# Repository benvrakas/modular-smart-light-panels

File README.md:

# Modular Smart Light Panels

Edge-lit hexagon, square and triangle light panels that snap together in any layout, work out their own arrangement, and play effects placed in the room rather than along a strip.

**Read the design in [SPEC.md](SPEC.md)**, with the reasons for each decision in [docs/decisions/](docs/decisions/). They are the only written description of the design; this page and the pictures only point into them. Progress toward the first prototype is tracked in [docs/roadmap-to-prototype.md](docs/roadmap-to-prototype.md).

| Close-up at an outside corner | Maximum brightness at night |
|---|---|
|  |  |

Other effects:

| Aurora | Sunset | Ocean |
|---|---|---|
|  |  |  |
| **Confetti** | **Warm white** | **Fire** |
|  |  |  |

Vertical (9:16):

| Outside corner | Painting wall | Inside corner |
|---|---|---|
|  |  |  |

Videos (1440p): [wide shot](docs/figures/video_wide.mp4) · [close-up](docs/figures/video_closeup.mp4).

## Where things are described

| Topic | Spec section | Pictures |
|---|---|---|
| Panels, shapes, optics | [§2](SPEC.md#2-physical-architecture--optical-design) |  |
| Seam contacts and bridge | [§3.3](SPEC.md#33-edge-contacts-and-bridge) |  |
| Edge and controller boards | [§3.5](SPEC.md#35-board-types-v60-decision-0009) |  |
| Topology discovery | [§4](SPEC.md#4-topology--orientation-discovery) | |
| Network, rendering, software | [§5–7](SPEC.md#5-network-topology) | |
| Power, brightness | [§8](SPEC.md#8-power-distribution--protection) |  |
| Mechanics (printed parts) | [§9](SPEC.md#9-mechanical) |  |

## Repository layout

```
SPEC.md                    The specification (version and changelog inside)
docs/
  decisions/               Decision records: context, options, choice, consequences
  figures/                 Generated pictures (make_figures.py); never edited by hand
  roadmap-to-prototype.md  Work packages and status
  gap-analysis.md, reviews/, mechanical/, datasheets/, bringup/, handoff/
  archive/explainer/       Retired HTML explainer (superseded by SPEC.md + figures)
hardware/                  KiCad 9: edge-board/, controller-board/, bridge/ (+ coupon/), lib/, archive/
mechanical/solidcraft/     Printed parts, assembly, STL/STEP exports, render/ (Blender scene scripts)
firmware/, software/       To be written
production/                Released fab packages, once ordered
```

Each design folder has its own notes (for example `hardware/edge-board/LAYOUT-NOTES.md`, `mechanical/solidcraft/README.md`) for how its files are built.

## Regenerating

- Figures: `python docs/figures/make_figures.py --all` (KiCad 3D views and SolidCraft snapshots, then the web copies).
- Renders: `python mechanical/solidcraft/render/render_batch.py` (Blender, GPU; slow). The penthouse scene file is not in git (over GitHub's file-size limit): get "Modern Loft Apartment" by Matteo Pascale from BlenderKit (free) into `mechanical/solidcraft/render/assets/penthouse/`, as described in `render/CREDITS.md`.

## License

Non-commercial use only: hardware, CAD and docs under CC BY-NC-SA 4.0, software under PolyForm Noncommercial 1.0.0. Details and third-party exceptions: [LICENSE.md](LICENSE.md).

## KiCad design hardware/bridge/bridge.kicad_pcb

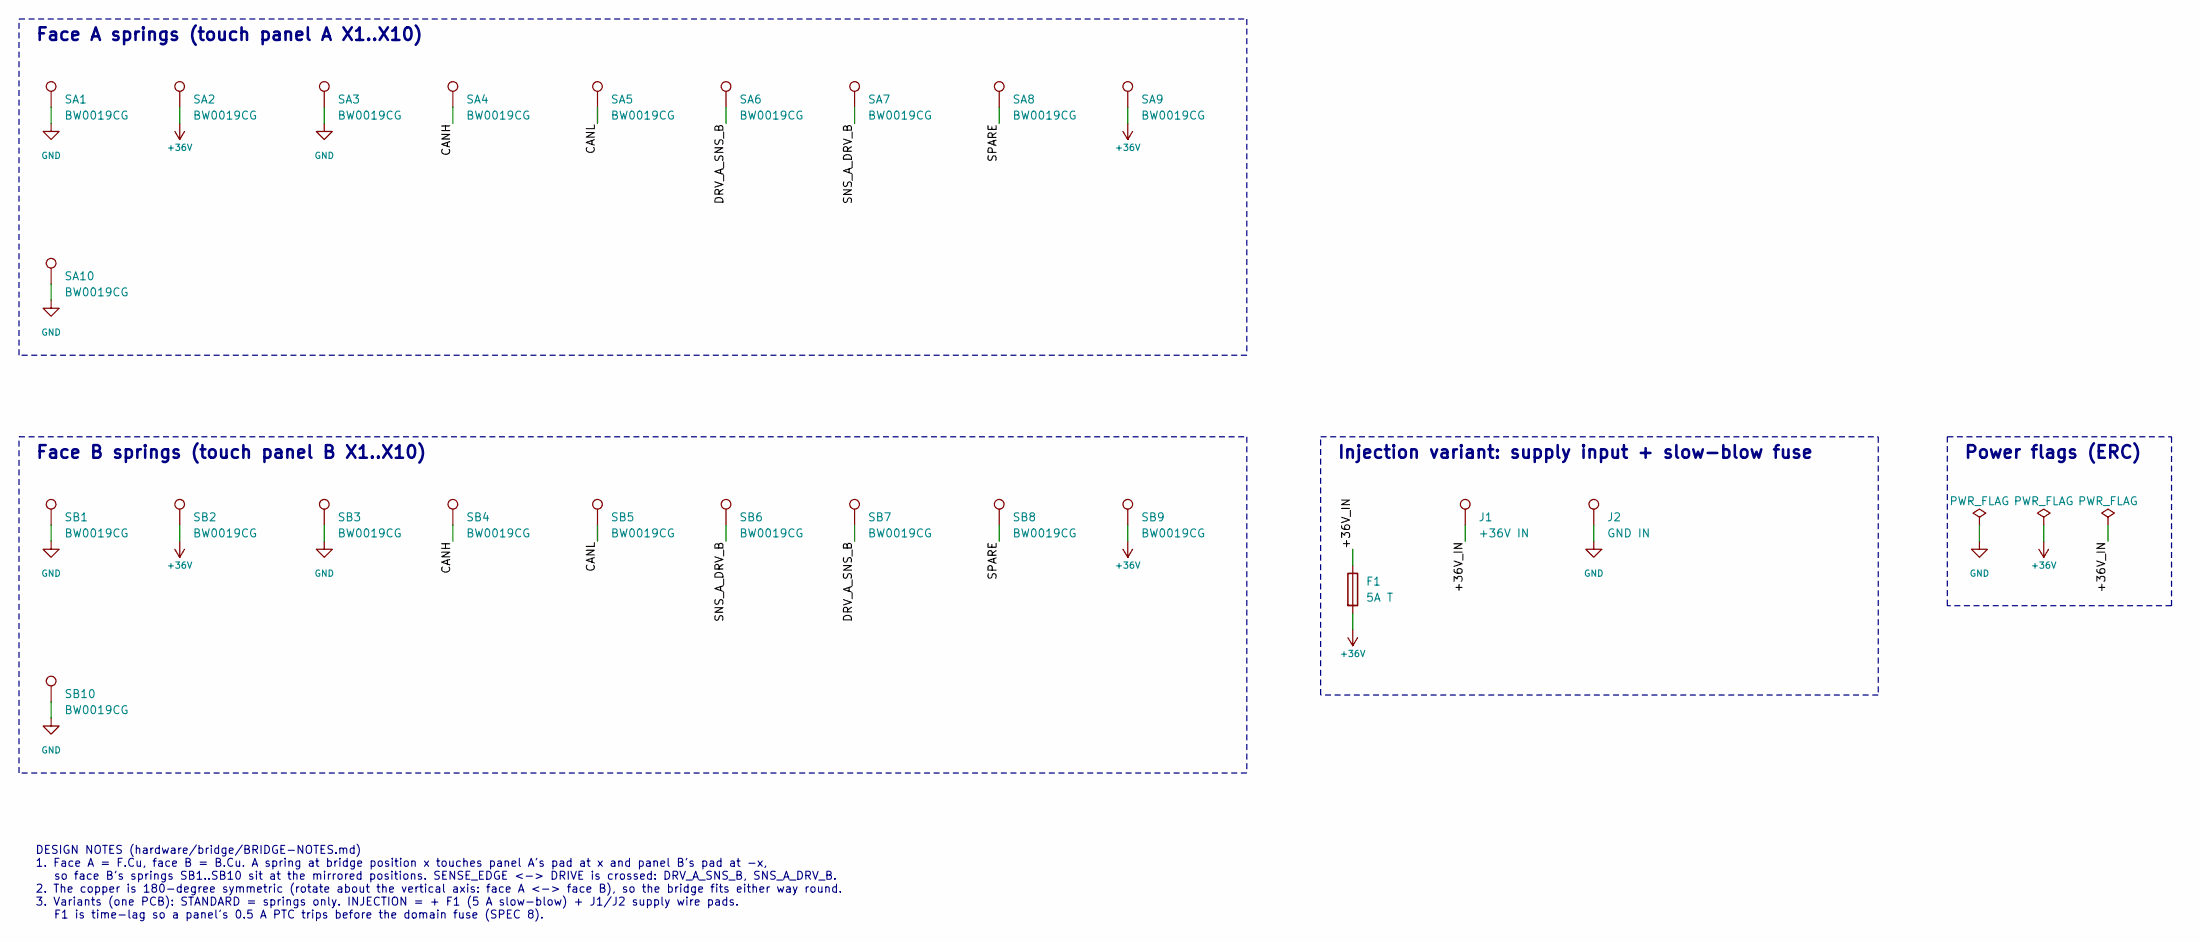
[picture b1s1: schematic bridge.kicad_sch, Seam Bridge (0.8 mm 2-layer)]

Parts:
F1: 5A T; Fuse_1206_3216Metric; MPN 0685T5000-01; LCSC C3163312
J1: +36V IN; SolderWire-0.75sqmm_1x01_D1.25mm_OD2.3mm
J2: GND IN; SolderWire-0.75sqmm_1x01_D1.25mm_OD2.3mm
SA1, SA2, SA3, SA4, SA5, SA6, SA7, SA8, SA9, SA10: BW0019CG; Spring_BW0019CG; MPN BW0019CG-L3.5W1.5H4.3; LCSC C2826517
SB1, SB2, SB3, SB4, SB5, SB6, SB7, SB8, SB9, SB10: BW0019CG; Spring_BW0019CG; MPN BW0019CG-L3.5W1.5H4.3; LCSC C2826517

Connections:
+36V: F1.2, SA2.1, SA9.1, SB2.1, SB9.1
/+36V_IN: F1.1, J1.1
/CANH: SA4.1, SB4.1
/CANL: SA5.1, SB5.1
/DRV_A_SNS_B: SA6.1, SB7.1
/SNS_A_DRV_B: SA7.1, SB6.1
/SPARE: SA8.1, SB8.1
GND: J2.1, SA1.1, SA3.1, SA10.1, SB1.1, SB3.1, SB10.1

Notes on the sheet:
Face A springs (touch panel A X1..X10)
Face B springs (touch panel B X1..X10)
Injection variant: supply input + slow-blow fuse
Power flags (ERC)
DESIGN NOTES (hardware/bridge/BRIDGE-NOTES.md) 1. Face A = F.Cu, face B = B.Cu. A spring at bridge position x touches panel A's pad at x and panel B's pad at -x, so face B's springs SB1..SB10 sit at the mirrored positions. SENSE_EDGE <-> DRIVE is crossed: DRV_A_SNS_B, SNS_A_DRV_B. 2. The copper is 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

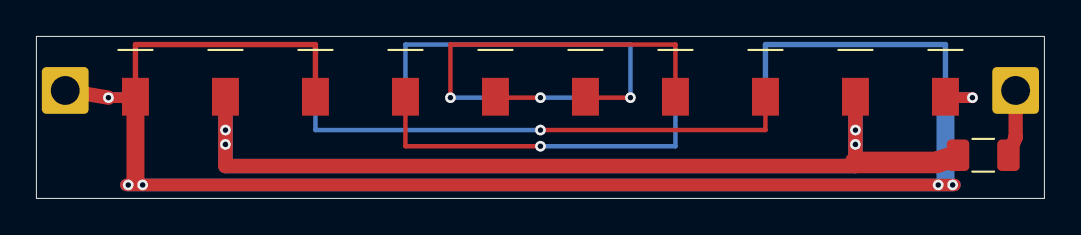
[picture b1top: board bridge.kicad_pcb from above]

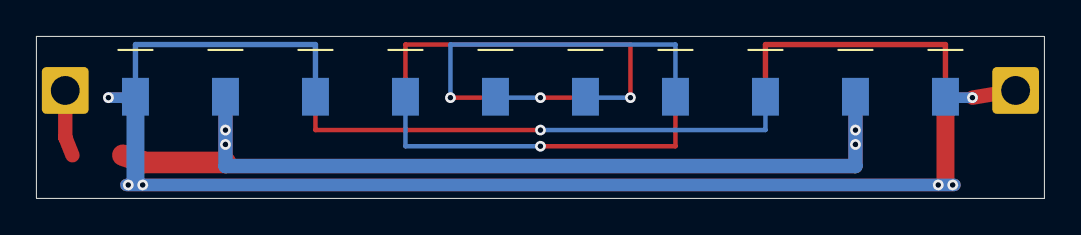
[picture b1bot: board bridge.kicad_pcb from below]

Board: 2 copper layers, 56.0 x 9.0 mm, 23 parts (10 on the bottom side), 8 nets.

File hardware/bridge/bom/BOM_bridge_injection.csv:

Comment,Designator,Footprint,LCSC
BW0019CG-L3.5W1.5H4.3,"SA1,SA2,SA3,SA4,SA5,SA6,SA7,SA8,SA9,SA10,SB1,SB2,SB3,SB4,SB5,SB6,SB7,SB8,SB9,SB10",Spring_BW0019CG,C2826517
0685T5000-01 5A slow-blow,F1,Fuse_1206_3216Metric,C3163312

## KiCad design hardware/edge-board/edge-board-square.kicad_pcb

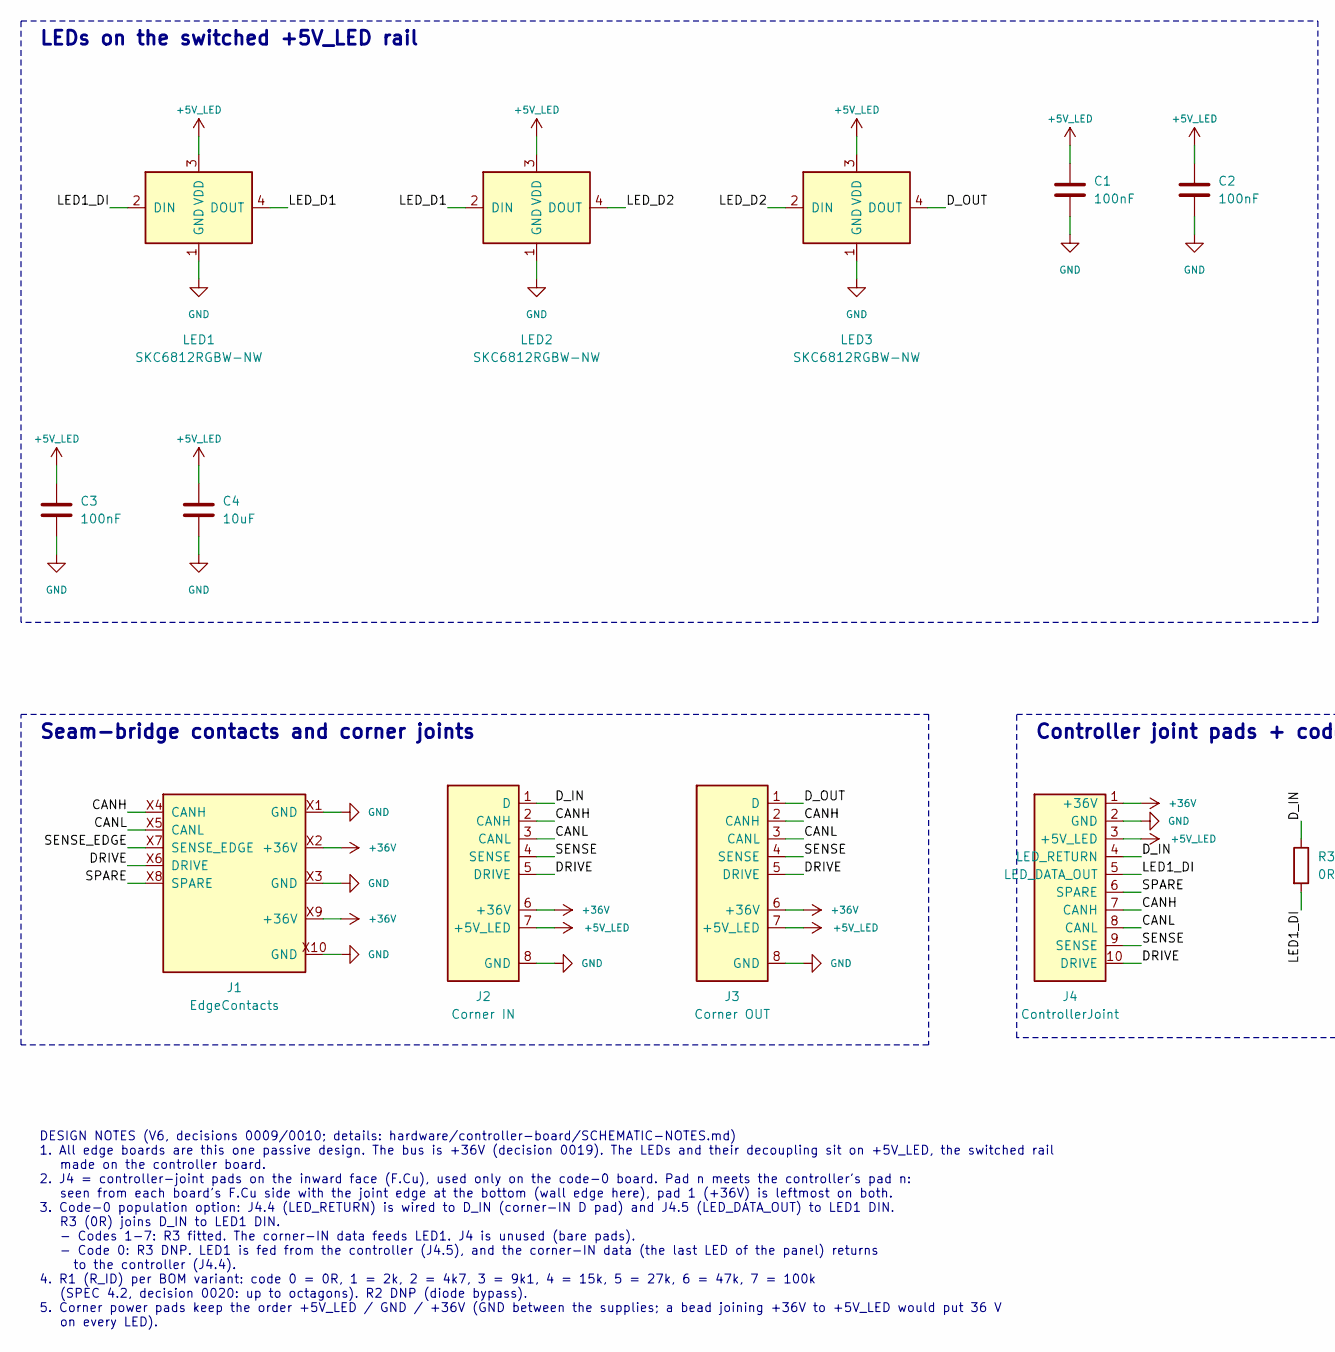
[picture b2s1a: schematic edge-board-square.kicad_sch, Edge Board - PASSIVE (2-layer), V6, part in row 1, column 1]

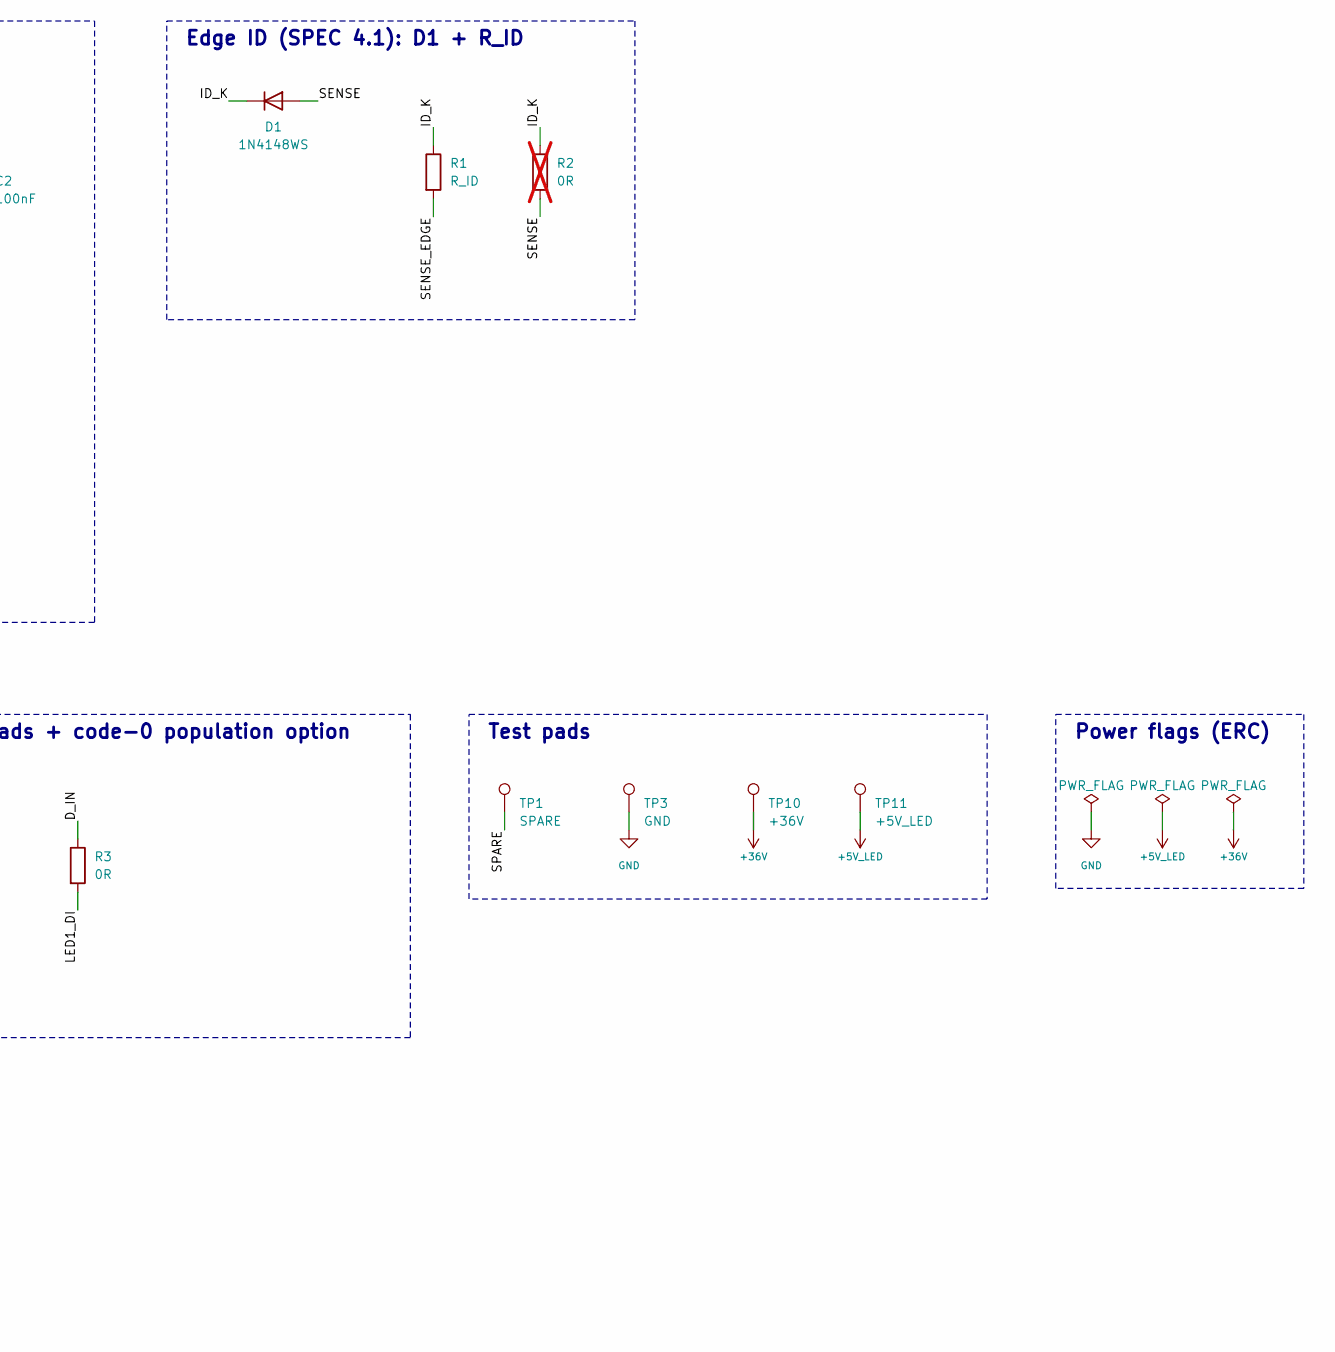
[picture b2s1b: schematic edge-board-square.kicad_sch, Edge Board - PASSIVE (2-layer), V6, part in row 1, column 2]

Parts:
C1, C2, C3: 100nF; C_0603_1608Metric; MPN CC0603KRX7R9BB104; LCSC C14663
C4: 10uF; C_0805_2012Metric; MPN CL21A106KAYNNNE; LCSC C15850
D1: 1N4148WS; D_SOD-323; MPN 1N4148WS; LCSC C2128
J1: EdgeContacts; EdgeContacts_SpringPads
J2: Corner IN; CornerJoint_L
J3: Corner OUT; CornerJoint_R
J4: ControllerJoint; ControllerJoint_EdgeBoard
LED1, LED2, LED3: SKC6812RGBW-NW; LED_SKC6812RGBW_5050-4; MPN SKC6812RGBW-NW; LCSC C5348912
R1: R_ID; R_0603_1608Metric; MPN 0603WAF2001T5E; LCSC C22975
R2: 0R; R_0603_1608Metric; MPN 0603WAF0000T5E; LCSC C21189; not fitted
R3: 0R; R_0402_1005Metric; MPN 0402WGF0000TCE; LCSC C17168
TP1: SPARE; TestPoint_Pad_D1.5mm
TP3: GND; TestPoint_Pad_D1.5mm
TP10: +36V; TestPoint_Pad_D1.5mm
TP11: +5V_LED; TestPoint_Pad_D1.5mm

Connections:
+5V_LED: C1.1, C2.1, C3.1, C4.1, J2.7 (+5V_LED), J3.7 (+5V_LED), J4.3 (+5V_LED), LED1.3 (VDD), LED2.3 (VDD), LED3.3 (VDD), TP11.1
+36V: J1.X2 (+36V), J1.X9 (+36V), J2.6 (+36V), J3.6 (+36V), J4.1 (+36V), TP10.1
/CANH: J1.X4 (CANH), J2.2 (CANH), J3.2 (CANH), J4.7 (CANH)
/CANL: J1.X5 (CANL), J2.3 (CANL), J3.3 (CANL), J4.8 (CANL)
/DRIVE: J1.X6 (DRIVE), J2.5 (DRIVE), J3.5 (DRIVE), J4.10 (DRIVE)
/D_IN: J2.1 (D), J4.4 (LED_RETURN), R3.1
/D_OUT: J3.1 (D), LED3.4 (DOUT)
/ID_K: D1.1 (K), R1.1, R2.1
/LED1_DI: J4.5 (LED_DATA_OUT), LED1.2 (DIN), R3.2
/LED_D1: LED1.4 (DOUT), LED2.2 (DIN)
/LED_D2: LED2.4 (DOUT), LED3.2 (DIN)
/SENSE: D1.2 (A), J2.4 (SENSE), J3.4 (SENSE), J4.9 (SENSE), R2.2
/SENSE_EDGE: J1.X7 (SENSE_EDGE), R1.2
/SPARE: J1.X8 (SPARE), J4.6 (SPARE), TP1.1
GND: C1.2, C2.2, C3.2, C4.2, J1.X1 (GND), J1.X3 (GND), J1.X10 (GND), J2.8 (GND), J3.8 (GND), J4.2 (GND), LED1.1 (GND), LED2.1 (GND), LED3.1 (GND), TP3.1

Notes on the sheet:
LEDs on the switched +5V_LED rail
Edge ID (SPEC 4.1): D1 + R_ID
Seam-bridge contacts and corner joints
Controller joint pads + code-0 population option
Test pads
Power flags (ERC)
DESIGN NOTES (V6, decisions 0009/0010; details: hardware/controller-board/SCHEMATIC-NOTES.md) 1. All edge boards are this one passive design. The bus is +36V (decision 0019). The LEDs and their decoupling sit on +5V_LED, the switched rail made on the controller board. 2. J4 = controller-joint pads 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

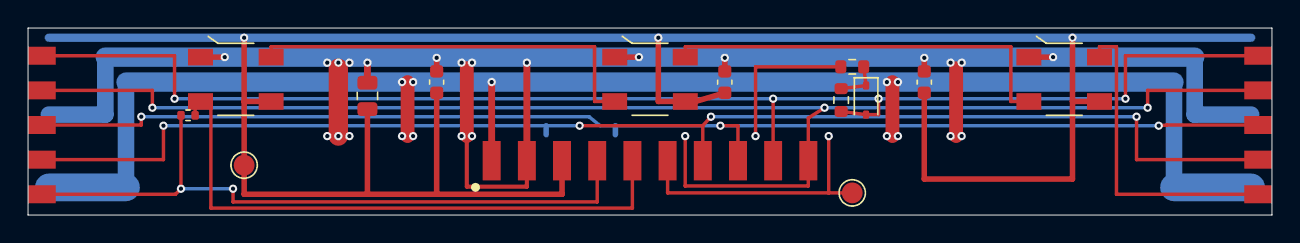
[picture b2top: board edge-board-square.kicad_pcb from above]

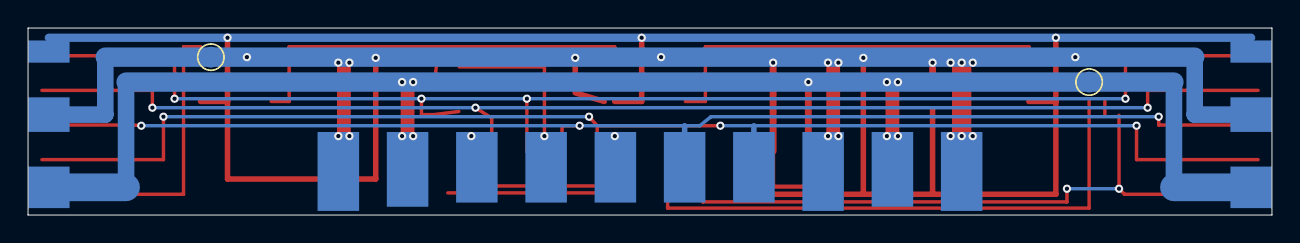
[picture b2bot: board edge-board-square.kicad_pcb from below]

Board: 2 copper layers, 89.8 x 13.5 mm, 19 parts (2 on the bottom side), 15 nets.

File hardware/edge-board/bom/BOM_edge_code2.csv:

Comment,Designator,Footprint,LCSC
100nF,"C1,C2,C3",C_0603_1608Metric,C14663
10uF,C4,C_0805_2012Metric,C15850
1N4148WS,D1,D_SOD-323,C2128
SKC6812RGBW-NW,"LED1,LED2,LED3",LED_SKC6812RGBW_5050-4,C5348912
2k7,R1,R_0603_1608Metric,C13167
0R,R3,R_0402_1005Metric,C17168

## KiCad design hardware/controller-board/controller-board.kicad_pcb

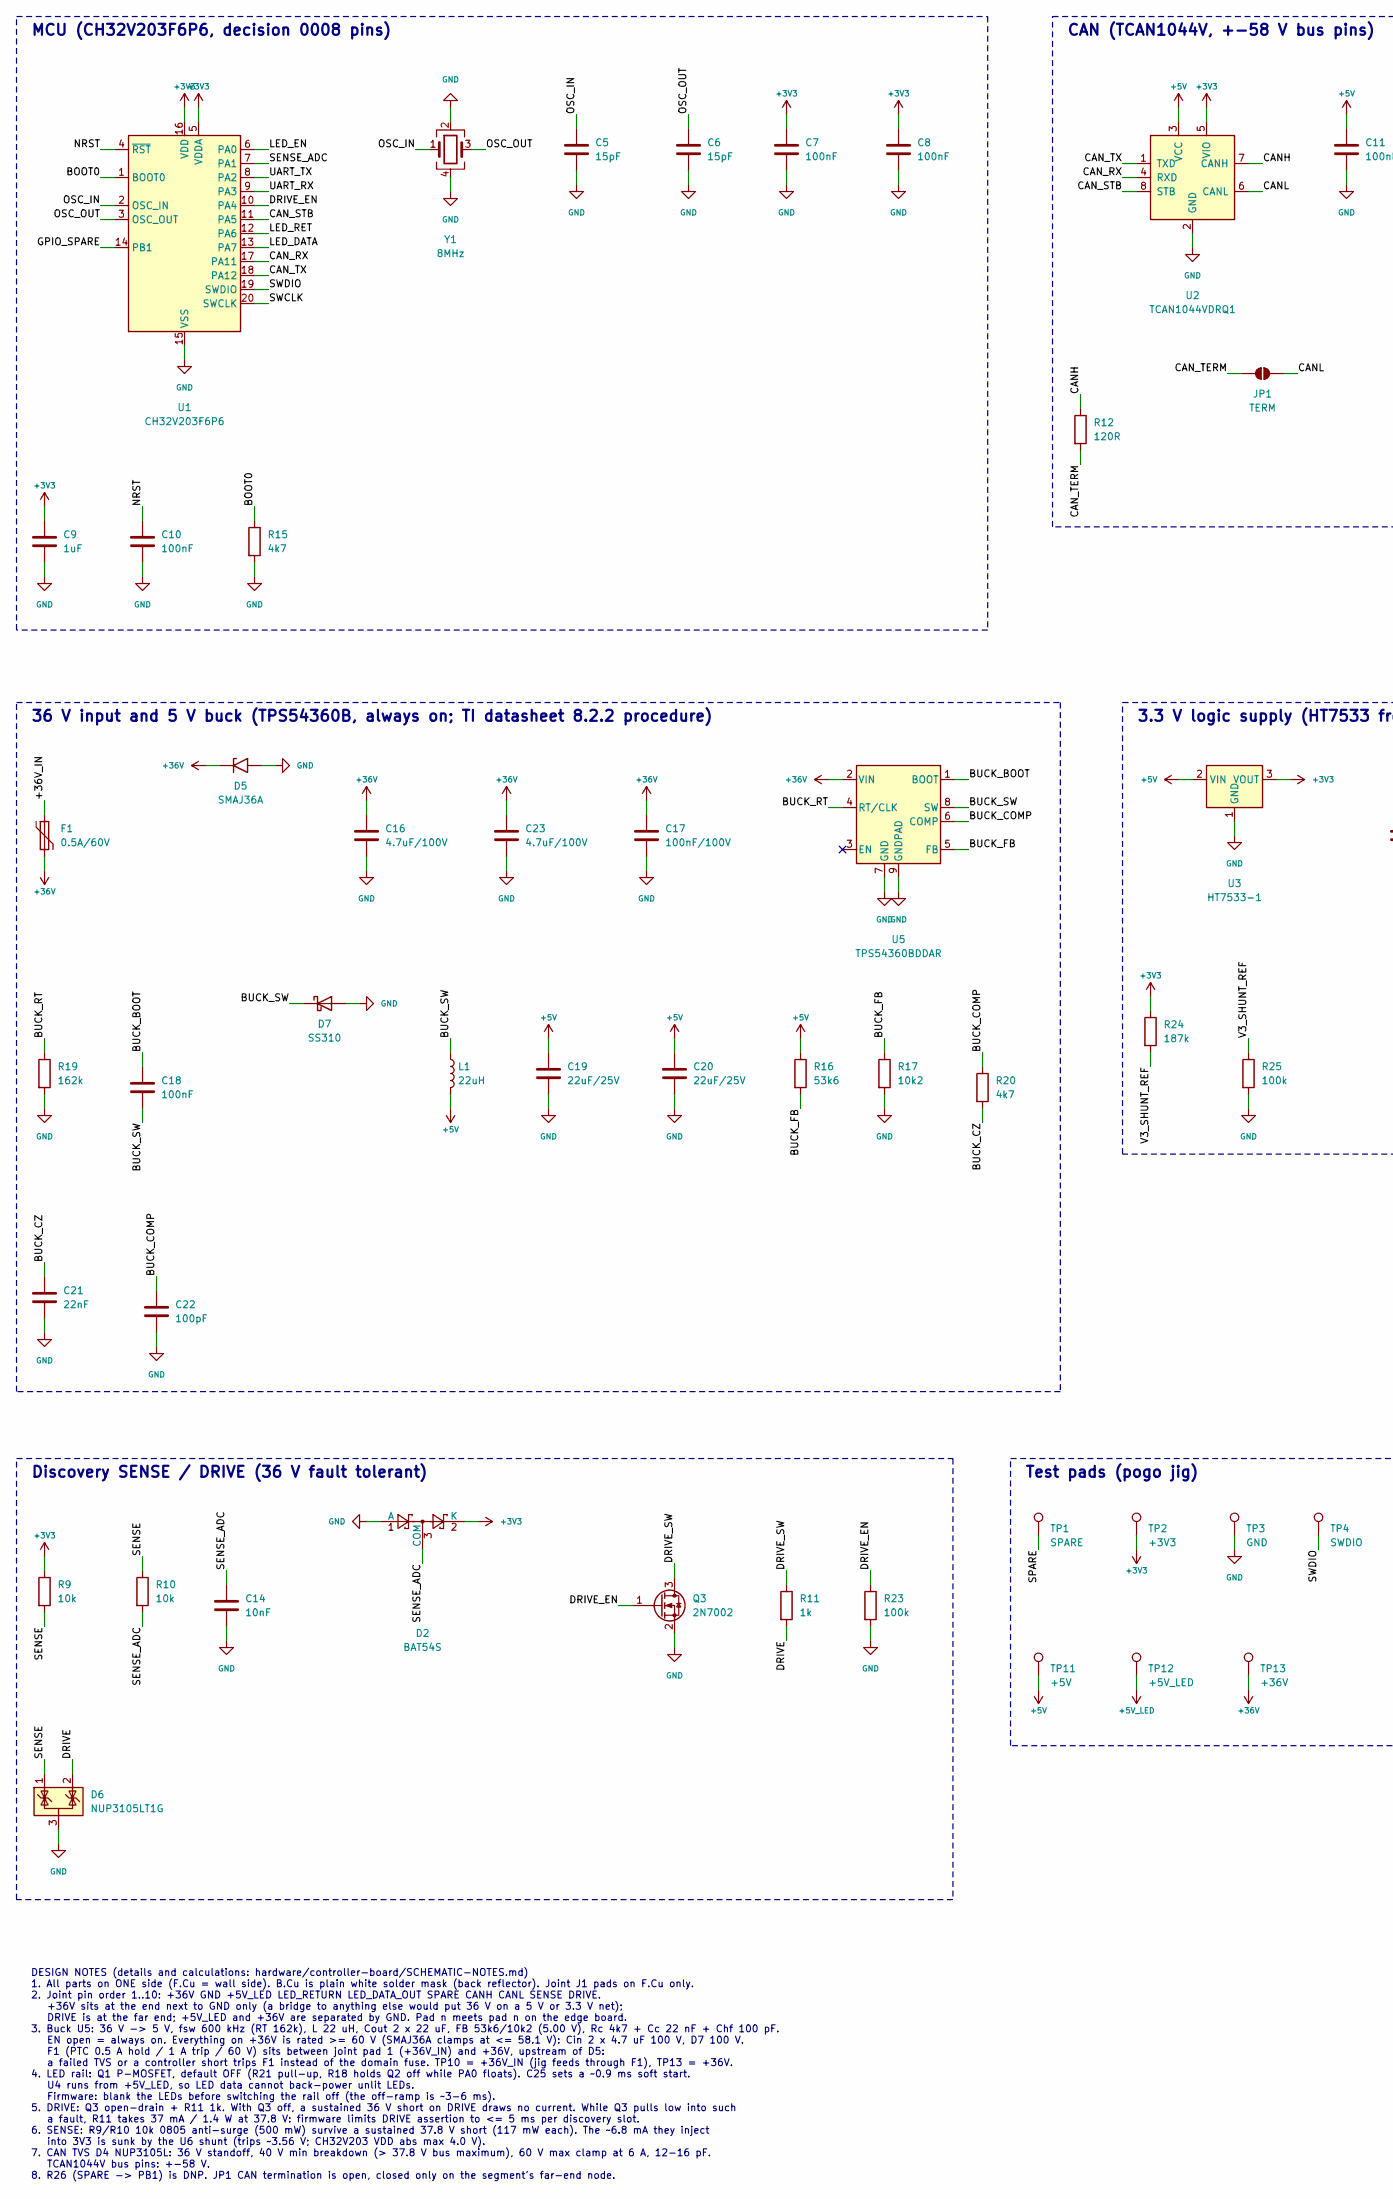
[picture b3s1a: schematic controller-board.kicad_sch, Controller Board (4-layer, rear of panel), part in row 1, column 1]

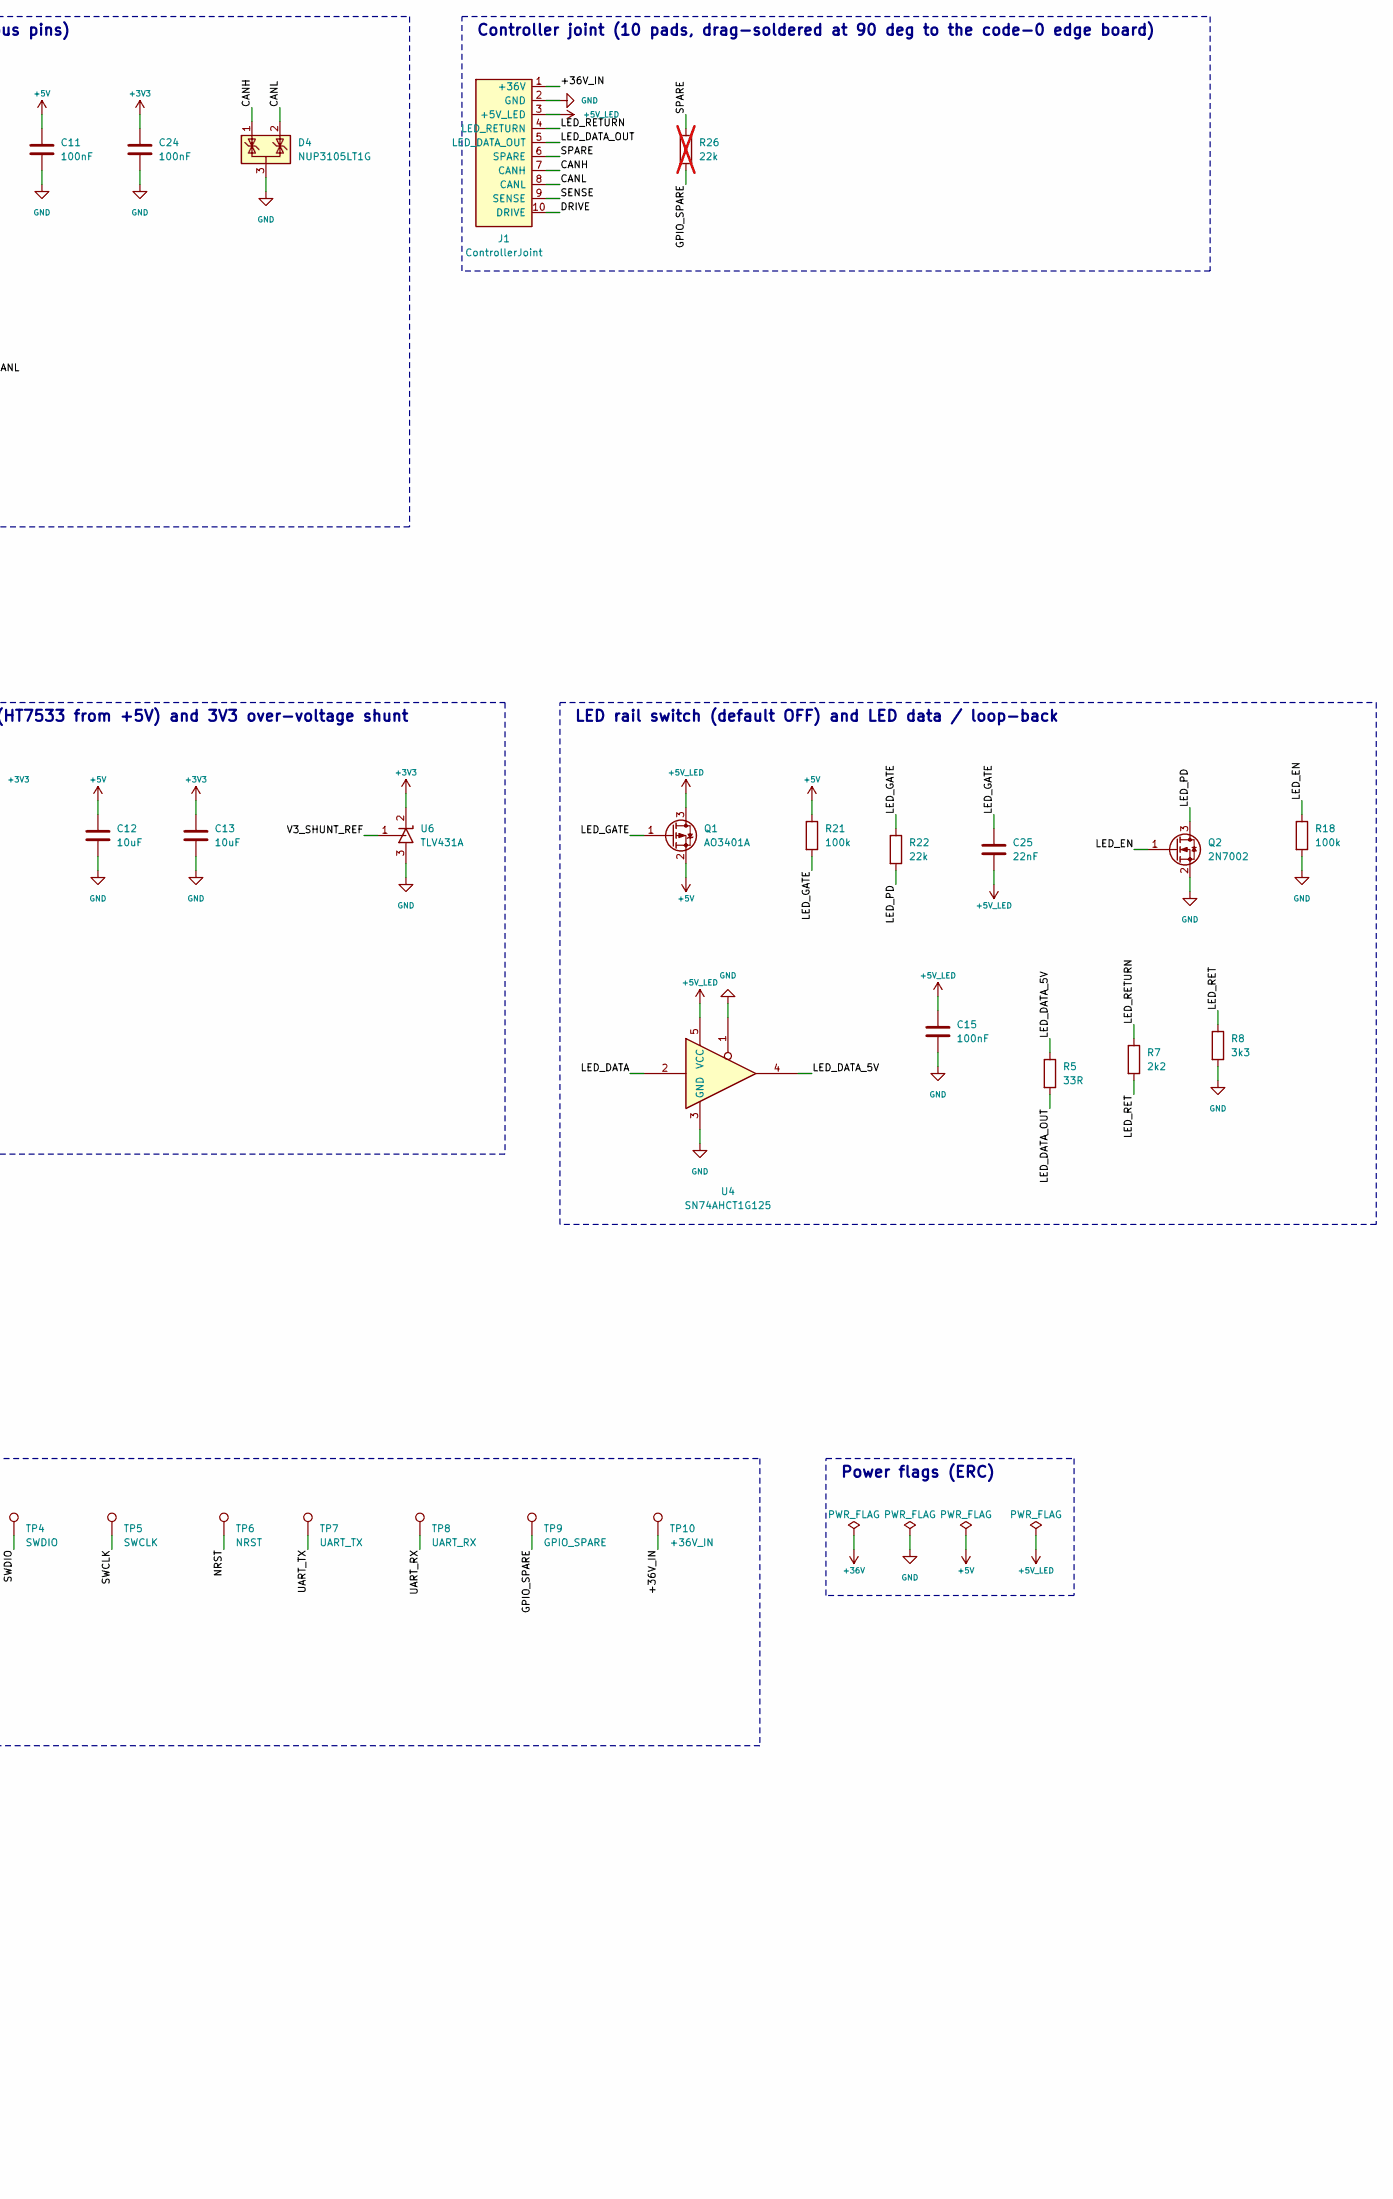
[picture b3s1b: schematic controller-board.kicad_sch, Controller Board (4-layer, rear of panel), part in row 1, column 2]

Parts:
C5, C6: 15pF; C_0603_1608Metric; MPN CL10C150JB8NNNC; LCSC C1644
C7, C8, C10, C11, C15, C18, C24: 100nF; C_0603_1608Metric; MPN CC0603KRX7R9BB104; LCSC C14663
C9: 1uF; C_0603_1608Metric; MPN CL10A105KB8NNNC; LCSC C15849
C12, C13: 10uF; C_0805_2012Metric; MPN CL21A106KAYNNNE; LCSC C15850
C14: 10nF; C_0603_1608Metric; MPN 0603B103K500NT; LCSC C57112
C16, C23: 4.7uF/100V; C_1206_3216Metric; MPN GRM31CC72A475KE11L; LCSC C237304
C17: 100nF/100V; C_0603_1608Metric; MPN CL10B104KC8NNNC; LCSC C15725
C19, C20: 22uF/25V; C_0805_2012Metric; MPN CL21A226MAQNNNE; LCSC C45783
C21, C25: 22nF; C_0603_1608Metric; MPN CL10B223KB8NNNC; LCSC C21122
C22: 100pF; C_0603_1608Metric; MPN CL10C101JB8NNNC; LCSC C14858
D2: BAT54S; SOT-23; MPN BAT54S,215; LCSC C47546
D4, D6: NUP3105LT1G; SOT-23; MPN NUP3105LT1G; LCSC C22390031
D5: SMAJ36A; D_SMA; MPN SMAJ36A-13-F; LCSC C134983
D7: SS310; D_SMA; MPN SS310; LCSC C15874
F1: 0.5A/60V; Fuse_1812_4532Metric; MPN mSMD050-60V; LCSC C70113
J1: ControllerJoint; ControllerJoint_ControllerEdge
JP1: TERM; SolderJumper-2_P1.3mm_Open_RoundedPad1.0x1.5mm
L1: 22uH; L_Changjiang_FNR6045S; MPN FNR6045S220MT; LCSC C168080
Q1: AO3401A; SOT-23; MPN AO3401A; LCSC C15127
Q2, Q3: 2N7002; SOT-23; MPN 2N7002; LCSC C8545
R5: 33R; R_0603_1608Metric; MPN 0603WAF330JT5E; LCSC C23140
R7: 2k2; R_0603_1608Metric; MPN 0603WAF2201T5E; LCSC C4190
R8: 3k3; R_0603_1608Metric; MPN 0603WAF3301T5E; LCSC C22978
R9, R10: 10k; R_0805_2012Metric; MPN ERJP06F1002V; LCSC C543567
R11: 1k; R_1206_3216Metric; MPN 1206W4F1001T5E; LCSC C4410
R12: 120R; R_0603_1608Metric; MPN 0603WAF1200T5E; LCSC C22787
R15, R20: 4k7; R_0603_1608Metric; MPN 0603WAF4701T5E; LCSC C23162
R16: 53k6; R_0603_1608Metric; MPN FRC0603F5362TS; LCSC C2930115
R17: 10k2; R_0603_1608Metric; MPN 0603WAF1022T5E; LCSC C22772
R18, R21, R23, R25: 100k; R_0603_1608Metric; MPN 0603WAF1003T5E; LCSC C25803
R19: 162k; R_0603_1608Metric; MPN 0603WAF1623T5E; LCSC C22815
R22: 22k; R_0603_1608Metric; MPN 0603WAF2202T5E; LCSC C31850
R24: 187k; R_0603_1608Metric; MPN 0603WAF1873T5E; LCSC C22896
R26: 22k; R_0603_1608Metric; MPN 0603WAF2202T5E; LCSC C31850; not fitted
TP1: SPARE; TestPoint_Pad_D1.5mm
TP2: +3V3; TestPoint_Pad_D1.5mm
TP3: GND; TestPoint_Pad_D1.5mm
TP4: SWDIO; TestPoint_Pad_D1.5mm
TP5: SWCLK; TestPoint_Pad_D1.5mm
TP6: NRST; TestPoint_Pad_D1.5mm
TP7: UART_TX; TestPoint_Pad_D1.5mm
TP8: UART_RX; TestPoint_Pad_D1.5mm
TP9: GPIO_SPARE; TestPoint_Pad_D1.5mm
TP10: +36V_IN; TestPoint_Pad_D1.5mm
TP11: +5V; TestPoint_Pad_D1.5mm
TP12: +5V_LED; TestPoint_Pad_D1.5mm
TP13: +36V; TestPoint_Pad_D1.5mm
U1: CH32V203F6P6; TSSOP-20_4.4x6.5mm_P0.65mm; MPN CH32V203F6P6; LCSC C3040880
U2: TCAN1044VDRQ1; SOIC-8_3.9x4.9mm_P1.27mm; MPN TCAN1044VDRQ1; LCSC C1852061
U3: HT7533-1; SOT-89-3; MPN HT7533-1; LCSC C14289
U4: SN74AHCT1G125; SOT-23-5; MPN SN74AHCT1G125DBVR; LCSC C20617903
U5: TPS54360BDDAR; TI_SO-PowerPAD-8_ThermalVias; MPN TPS54360BDDAR; LCSC C524806
U6: TLV431A; SOT-23; MPN TLV431AIDBZR; LCSC C56765
Y1: 8MHz; Crystal_SMD_3225-4Pin_3.2x2.5mm; MPN XL2EL89COI-111YLC-8M; LCSC C2973805

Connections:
+3V3: C7.1, C8.1, C9.1, C13.1, C24.1, D2.2 (K), R9.1, R24.1, TP2.1, U1.5 (VDDA), U1.16 (VDD), U2.5 (VIO), U3.3 (VOUT), U6.2 (K)
+5V: C11.1, C12.1, C19.1, C20.1, L1.2, Q1.2 (S), R16.1, R21.1, TP11.1, U2.3 (VCC), U3.2 (VIN)
+5V_LED: C15.1, C25.2, J1.3 (+5V_LED), Q1.3 (D), TP12.1, U4.5 (VCC)
+36V: C16.1, C17.1, C23.1, D5.1 (A1), F1.2, TP13.1, U5.2 (VIN)
/+36V_IN: F1.1, J1.1 (+36V), TP10.1
/BOOT0: R15.1, U1.1 (BOOT0)
/BUCK_BOOT: C18.1, U5.1 (BOOT)
/BUCK_COMP: C22.1, R20.1, U5.6 (COMP)
/BUCK_CZ: C21.1, R20.2
/BUCK_FB: R16.2, R17.1, U5.5 (FB)
/BUCK_RT: R19.1, U5.4 (RT/CLK)
/BUCK_SW: C18.2, D7.1 (K), L1.1, U5.8 (SW)
/CANH: D4.1 (K), J1.7 (CANH), R12.1, U2.7 (CANH)
/CANL: D4.2 (K), J1.8 (CANL), JP1.2 (B), U2.6 (CANL)
/CAN_RX: U1.17 (PA11), U2.4 (RXD)
/CAN_STB: U1.11 (PA5), U2.8 (STB)
/CAN_TERM: JP1.1 (A), R12.2
/CAN_TX: U1.18 (PA12), U2.1 (TXD)
/DRIVE: D6.2 (K), J1.10 (DRIVE), R11.2
/DRIVE_EN: Q3.1 (G), R23.1, U1.10 (PA4)
/DRIVE_SW: Q3.3 (D), R11.1
/GPIO_SPARE: R26.2, TP9.1, U1.14 (PB1)
/LED_DATA: U1.13 (PA7), U4.2
/LED_DATA_5V: R5.1, U4.4
/LED_DATA_OUT: J1.5 (LED_DATA_OUT), R5.2
/LED_EN: Q2.1 (G), R18.1, U1.6 (PA0)
/LED_GATE: C25.1, Q1.1 (G), R21.2, R22.1
/LED_PD: Q2.3 (D), R22.2
/LED_RET: R7.2, R8.1, U1.12 (PA6)
/LED_RETURN: J1.4 (LED_RETURN), R7.1
/NRST: C10.1, TP6.1, U1.4 (~RST)
/OSC_IN: C5.1, U1.2 (OSC_IN), Y1.1
/OSC_OUT: C6.1, U1.3 (OSC_OUT), Y1.3
/SENSE: D6.1 (K), J1.9 (SENSE), R9.2, R10.1
/SENSE_ADC: C14.1, D2.3 (COM), R10.2, U1.7 (PA1)
/SPARE: J1.6 (SPARE), R26.1, TP1.1
/SWCLK: TP5.1, U1.20 (SWCLK)
/SWDIO: TP4.1, U1.19 (SWDIO)
/UART_RX: TP8.1, U1.9 (PA3)
/UART_TX: TP7.1, U1.8 (PA2)
/V3_SHUNT_REF: R24.2, R25.1, U6.1 (REF)
GND: C5.2, C6.2, C7.2, C8.2, C9.2, C10.2, C11.2, C12.2, C13.2, C14.2, C15.2, C16.2, C17.2, C19.2, C20.2, C21.2, C22.2, C23.2, C24.2, D2.1 (A), D4.3 (A), D5.2 (A2), D6.3 (A), D7.2 (A), J1.2 (GND), Q2.2 (S), Q3.2 (S), R8.2, R15.2, R17.2, R18.2, R19.2, R23.2, R25.2, TP3.1, U1.15 (VSS), U2.2 (GND), U3.1 (GND), U4.1, U4.3 (GND), U5.7 (GND), U5.9 (GNDPAD), U6.3 (A), Y1.2, Y1.4

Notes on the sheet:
MCU (CH32V203F6P6, decision 0008 pins)
CAN (TCAN1044V, +-58 V bus pins)
Controller joint (10 pads, drag-soldered at 90 deg to the code-0 edge board)
36 V input and 5 V buck (TPS54360B, always on; TI datasheet 8.2.2 procedure)
3.3 V logic supply (HT7533 from +5V) and 3V3 over-voltage shunt
LED rail switch (default OFF) and LED data / loop-back
Discovery SENSE / DRIVE (36 V fault tolerant)
Test pads (pogo jig)
Power flags (ERC)
DESIGN NOTES (details and calculations: hardware/controller-board/SCHEMATIC-NOTES.md) 1. All parts on ONE side (F.Cu = wall side). B.Cu is plain white solder mask (back reflector). Joint J1 pads on F.Cu only. 2. Joint pin order 1..10: +36V GND +5V_LED LED_RETURN LED_DATA_OUT SPARE CANH CANL SENSE D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

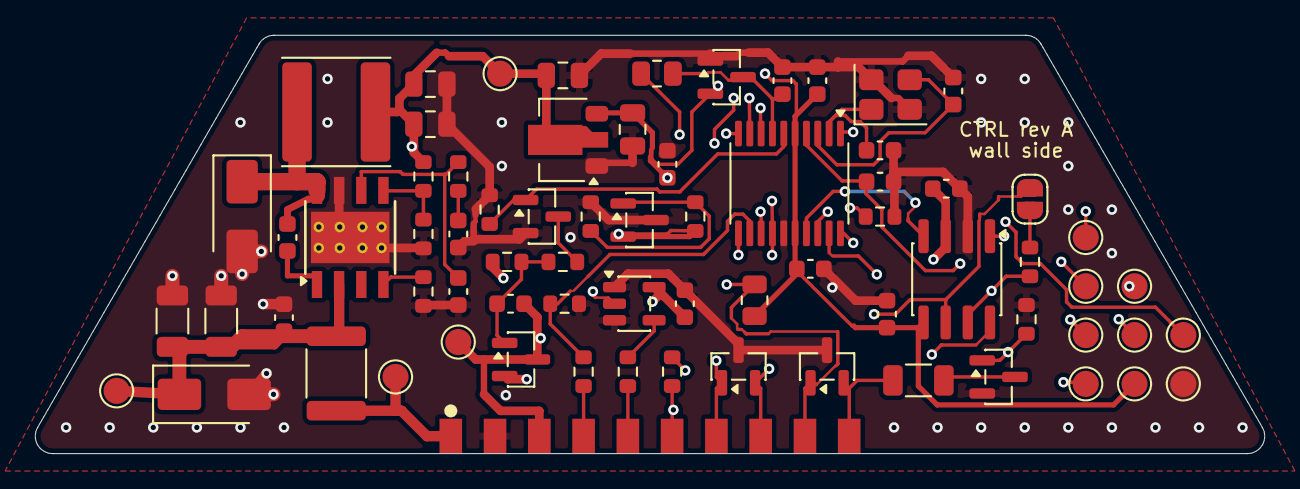
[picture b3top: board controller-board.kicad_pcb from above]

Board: 4 copper layers, 70.5 x 24.0 mm, 72 parts (0 on the bottom side), 42 nets.

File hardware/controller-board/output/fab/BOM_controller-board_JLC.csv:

Comment,Designator,Footprint,LCSC
15pF,"C5,C6",C_0603_1608Metric,C1644
100nF,"C7,C8,C10,C11,C15,C18,C24",C_0603_1608Metric,C14663
1uF,C9,C_0603_1608Metric,C15849
10uF,"C12,C13",C_0805_2012Metric,C15850
10nF,C14,C_0603_1608Metric,C57112
4.7uF/100V,"C16,C23",C_1206_3216Metric,C237304
100nF/100V,C17,C_0603_1608Metric,C15725
22uF/25V,"C19,C20",C_0805_2012Metric,C45783
22nF,"C21,C25",C_0603_1608Metric,C21122
100pF,C22,C_0603_1608Metric,C14858
BAT54S,D2,SOT-23,C47546
NUP3105LT1G,"D4,D6",SOT-23,C22390031
SMAJ36A,D5,D_SMA,C134983
SS310,D7,D_SMA,C15874
0.5A/60V,F1,Fuse_1812_4532Metric,C70113
22uH,L1,L_Changjiang_FNR6045S,C168080
AO3401A,Q1,SOT-23,C15127
2N7002,"Q2,Q3",SOT-23,C8545
33R,R5,R_0603_1608Metric,C23140
2k2,R7,R_0603_1608Metric,C4190
3k3,R8,R_0603_1608Metric,C22978
10k,"R9,R10",R_0805_2012Metric,C543567
1k,R11,R_1206_3216Metric,C4410
120R,R12,R_0603_1608Metric,C22787
4k7,"R15,R20",R_0603_1608Metric,C23162
53k6,R16,R_0603_1608Metric,C2930115
10k2,R17,R_0603_1608Metric,C22772
100k,"R18,R21,R23,R25",R_0603_1608Metric,C25803
162k,R19,R_0603_1608Metric,C22815
22k,R22,R_0603_1608Metric,C31850
187k,R24,R_0603_1608Metric,C22896
CH32V203F6P6,U1,TSSOP-20_4.4x6.5mm_P0.65mm,C3040880
TCAN1044VDRQ1,U2,SOIC-8_3.9x4.9mm_P1.27mm,C1852061
HT7533-1,U3,SOT-89-3,C14289
SN74AHCT1G125,U4,SOT-23-5,C20617903
TPS54360BDDAR,U5,TI_SO-PowerPAD-8_ThermalVias,C524806
TLV431A,U6,SOT-23,C56765
8MHz,Y1,Crystal_SMD_3225-4Pin_3.2x2.5mm,C2973805
